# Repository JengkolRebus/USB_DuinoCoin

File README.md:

# DUINOCOIN USB MINER
 USB MINER FOR DUINOCOIN

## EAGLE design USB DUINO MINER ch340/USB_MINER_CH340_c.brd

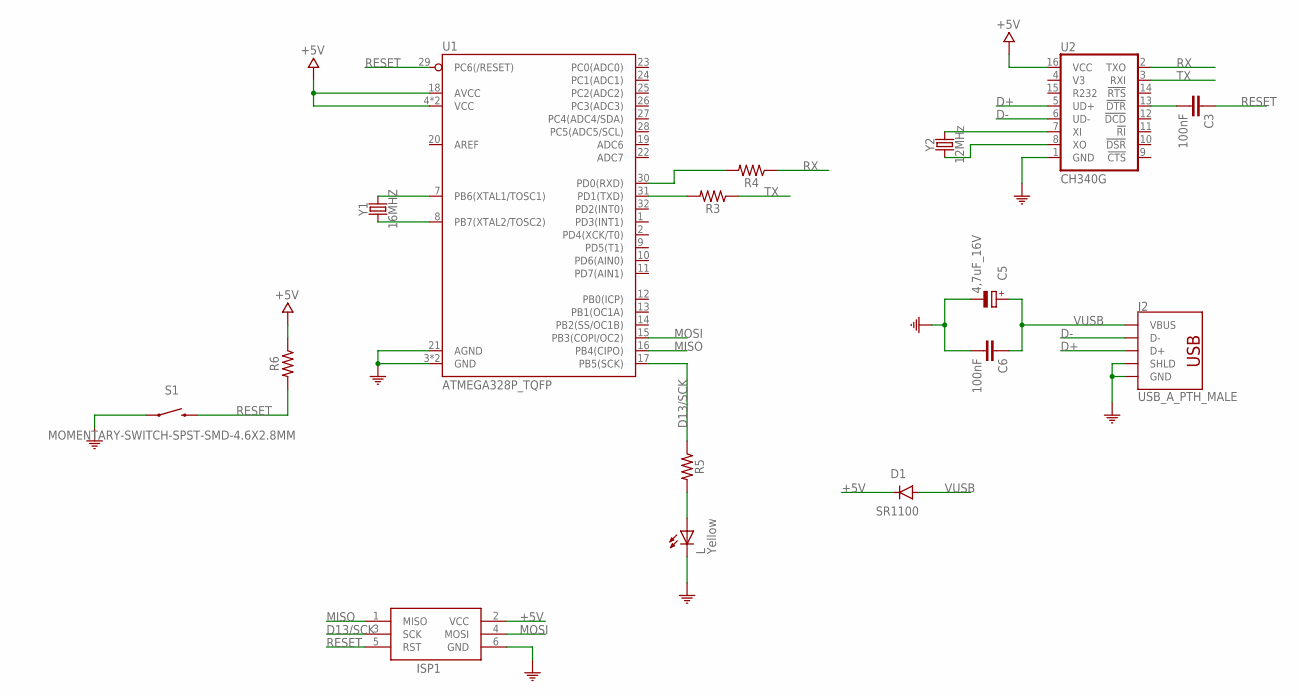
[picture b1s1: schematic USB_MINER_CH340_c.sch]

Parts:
C3, C6: 100nF; C0805K
C5: 4,7uF_16V; TAN-A
D1: SR1100; DO-214AC
ISP1: AVRISP-6; AVRISP
J2: USB_A_PTH_MALE; USB-A-H
L: Yellow; CHIPLED_0805
R3, R4, R5, R6: 1k; R0805
S1: MOMENTARY-SWITCH-SPST-SMD-4.6X2.8MM; TACTILE_SWITCH_SMD_4.6X2.8MM
U1: ATMEGA328P_TQFP; TQFP32-08
U2: CH340G; SO016
Y1: 16MHZ; HC49UP
Y2: 12MHz; HC49UP

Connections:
+5V: D1.C, ISP1.2 (VCC), R6.1, U1.4 (VCC), U1.6 (VCC), U1.18 (AVCC), U2.16 (VCC)
COM: C5.2 (-), C6.2, ISP1.6 (GND), J2.GND, J2.SHLD1 (SHLD), J2.SHLD2 (SHLD), L.C, S1.1, S1.2 (1), U1.3 (GND), U1.5 (GND), U1.21 (AGND), U2.1 (GND)
D13/SCK: ISP1.3 (SCK), R5.1, U1.17 (PB5(SCK))
D+: J2.D+, U2.5 (UD+)
D-: J2.D-, U2.6 (UD-)
MISO: ISP1.1 (MISO), U1.16 (PB4(CIPO))
MOSI: ISP1.4 (MOSI), U1.15 (PB3(COPI/OC2))
unnamed: U2.7 (XI), Y2.2
unnamed: U2.8 (XO), Y2.1
unnamed: U1.7 (PB6(XTAL1/TOSC1)), Y1.2
unnamed: L.A, R5.2
unnamed: U1.8 (PB7(XTAL2/TOSC2)), Y1.1
unnamed: R3.2, U1.31 (PD1(TXD))
unnamed: R4.2, U1.30 (PD0(RXD))
unnamed: C3.2, U2.13 (!DTR)
RESET: C3.1, ISP1.5 (RST), R6.2, S1.3 (2), S1.4 (2), U1.29 (PC6(/RESET))
RX: R4.1, U2.2 (TXO)
TX: R3.1, U2.3 (RXI)
VUSB: C5.1 (+), C6.1, D1.A, J2.VBUS

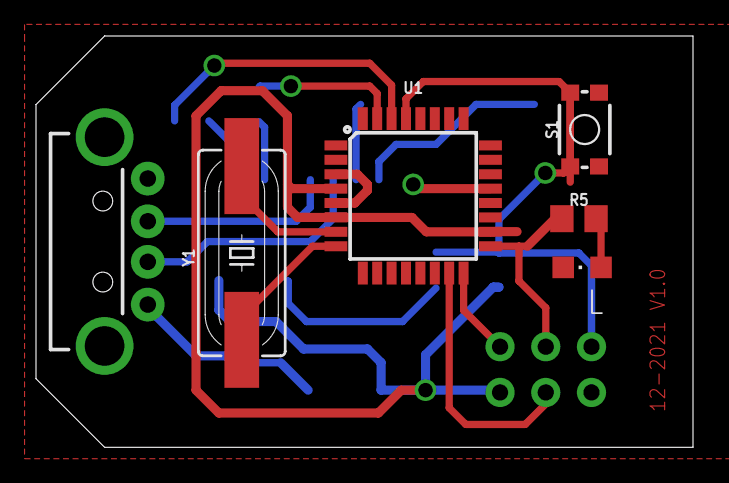
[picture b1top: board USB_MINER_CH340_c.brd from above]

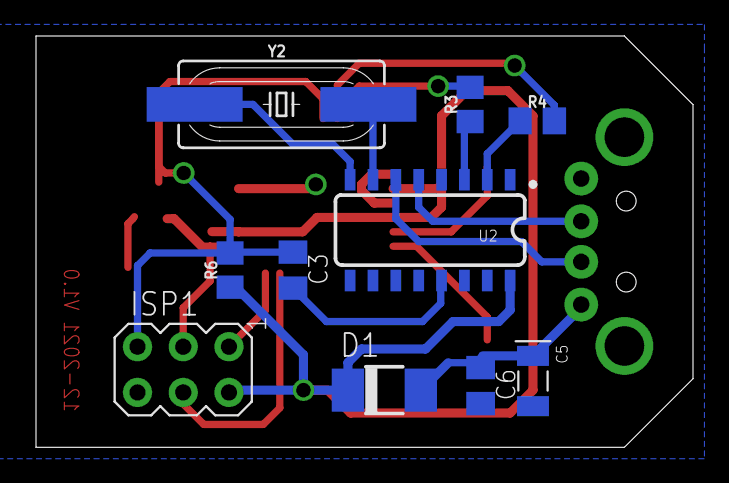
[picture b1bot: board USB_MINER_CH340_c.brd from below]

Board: 2 copper layers, 36.5 x 22.9 mm, 16 parts (10 on the bottom side), 19 nets.

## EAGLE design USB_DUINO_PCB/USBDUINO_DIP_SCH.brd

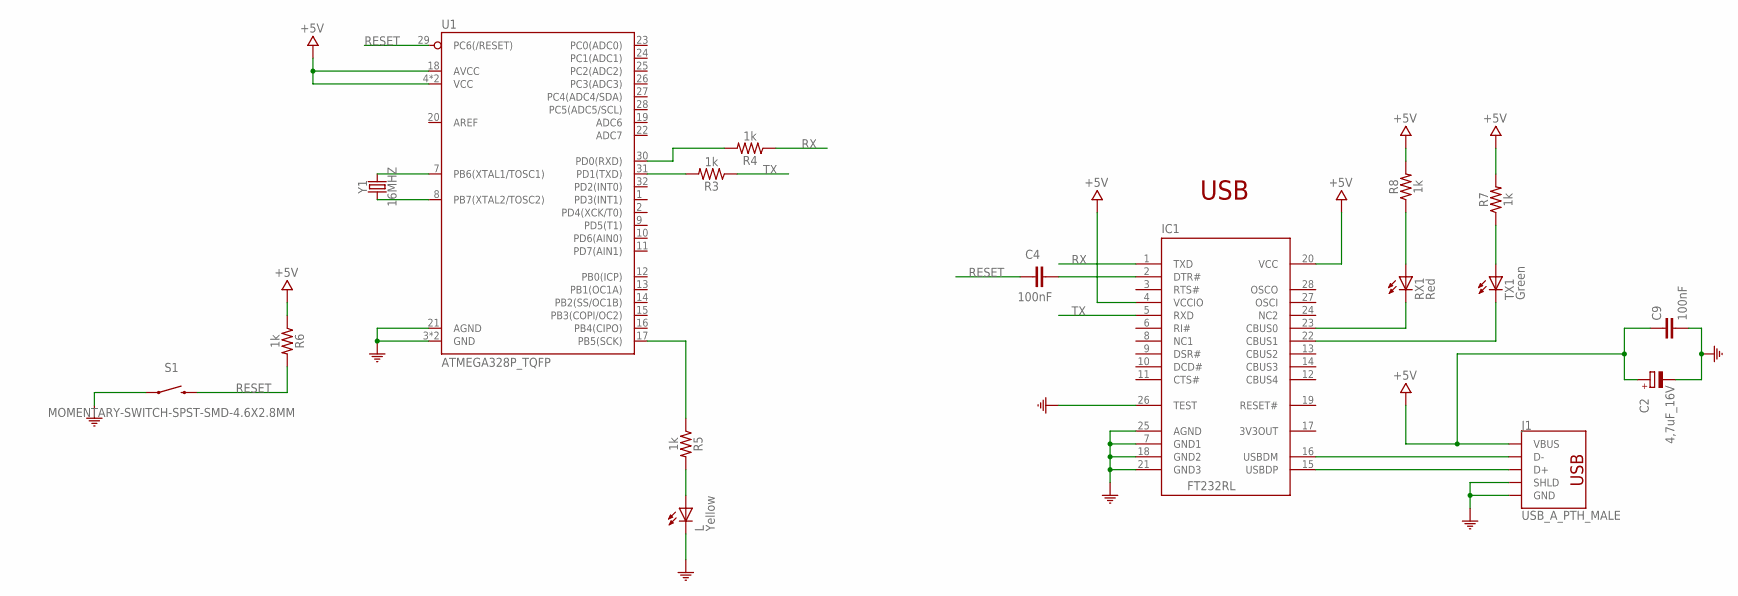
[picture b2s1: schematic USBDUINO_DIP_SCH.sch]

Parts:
C2: 4,7uF_16V; TAN-A
C4, C9: 100nF; C0603-ROUND
IC1: FT232RL; SSOP28
J1: USB_A_PTH_MALE; USB-A-H
L: Yellow; CHIPLED_0805
R3, R4, R5, R6, R7, R8: 1k; 0603
RX1: Red; CHIPLED_0805
S1: MOMENTARY-SWITCH-SPST-SMD-4.6X2.8MM; TACTILE_SWITCH_SMD_4.6X2.8MM
TX1: Green; CHIPLED_0805
U1: ATMEGA328P_TQFP; TQFP32-08
Y1: 16MHZ; HC49UP

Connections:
3V3OUT: IC1.17 (3V3OUT)
+5V: C2.1 (+), C9.1, IC1.4 (VCCIO), IC1.20 (VCC), J1.VBUS, R6.1, R7.2, R8.2, U1.4 (VCC), U1.6 (VCC), U1.18 (AVCC)
COM: C2.2 (-), C9.2, IC1.7 (GND1), IC1.18 (GND2), IC1.21 (GND3), IC1.25 (AGND), IC1.26 (TEST), J1.GND, J1.SHLD1 (SHLD), J1.SHLD2 (SHLD), L.C, S1.1, S1.2 (1), U1.3 (GND), U1.5 (GND), U1.21 (AGND)
D13/SCK: R5.1, U1.17 (PB5(SCK))
unnamed: U1.7 (PB6(XTAL1/TOSC1)), Y1.2
unnamed: C4.2, IC1.2 (DTR#)
unnamed: IC1.15 (USBDP), J1.D+
unnamed: IC1.16 (USBDM), J1.D-
unnamed: L.A, R5.2
unnamed: IC1.23 (CBUS0), RX1.C
unnamed: IC1.22 (CBUS1), TX1.C
unnamed: U1.8 (PB7(XTAL2/TOSC2)), Y1.1
unnamed: R7.1, TX1.A
unnamed: R3.2, U1.31 (PD1(TXD))
unnamed: R4.2, U1.30 (PD0(RXD))
unnamed: R8.1, RX1.A
RESET: C4.1, R6.2, S1.3 (2), S1.4 (2), U1.29 (PC6(/RESET))
RX: IC1.1 (TXD), R4.1
TX: IC1.5 (RXD), R3.1

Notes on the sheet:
USB

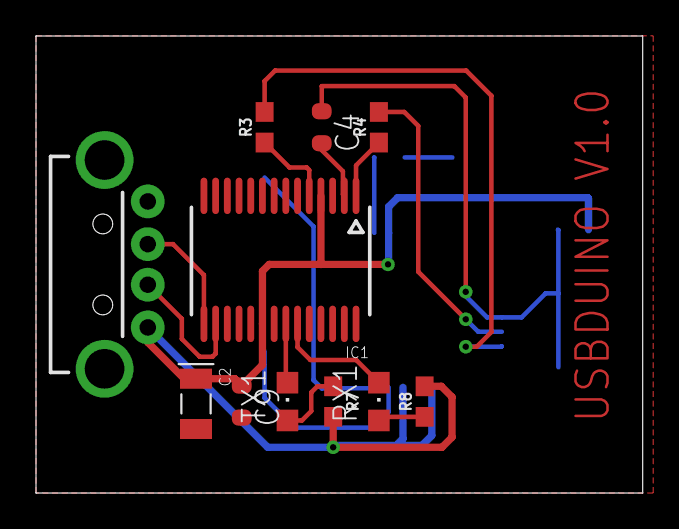
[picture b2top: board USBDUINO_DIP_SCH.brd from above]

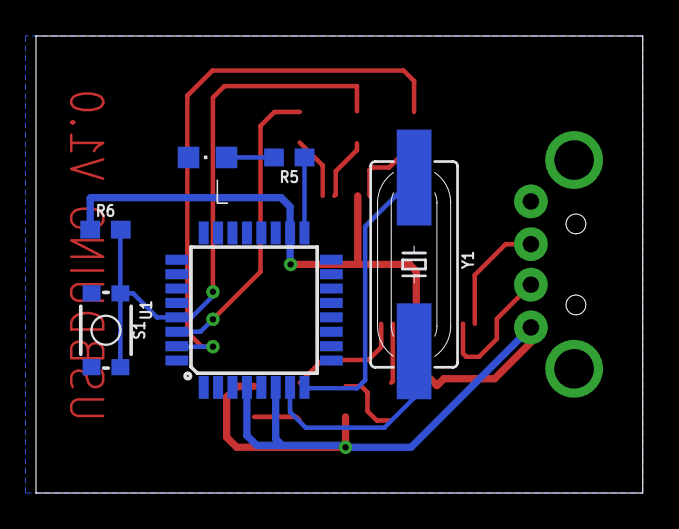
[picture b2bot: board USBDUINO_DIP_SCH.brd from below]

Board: 2 copper layers, 33.7 x 25.4 mm, 17 parts (6 on the bottom side), 18 nets.

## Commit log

2021-12-13 Add new sketch for CH340
2021-12-13 Revisi board ch340
2021-12-14 update part
    ubah part dengan ukuran 0603 menjadi 0805
2021-12-14 ganti tulisan versi di board
    bulan-tahun versi
2021-12-19 buat file cdr untuk cetak pcb

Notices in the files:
parts and their libraries:
SparkFun-Connectors: Licensing: Creative Commons ShareAlike 4.0 International - https://creativecommons.org/licenses/by-sa/4.0
